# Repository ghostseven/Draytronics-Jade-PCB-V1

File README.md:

# Draytronics-Jade-PCB-V1

## Currently untested pre-production only.

An open source 65% mechanical keyboard, designed to be easily built with through hole components. More info / kits / PCB designs available at https://www.draytronics.co.uk/jade

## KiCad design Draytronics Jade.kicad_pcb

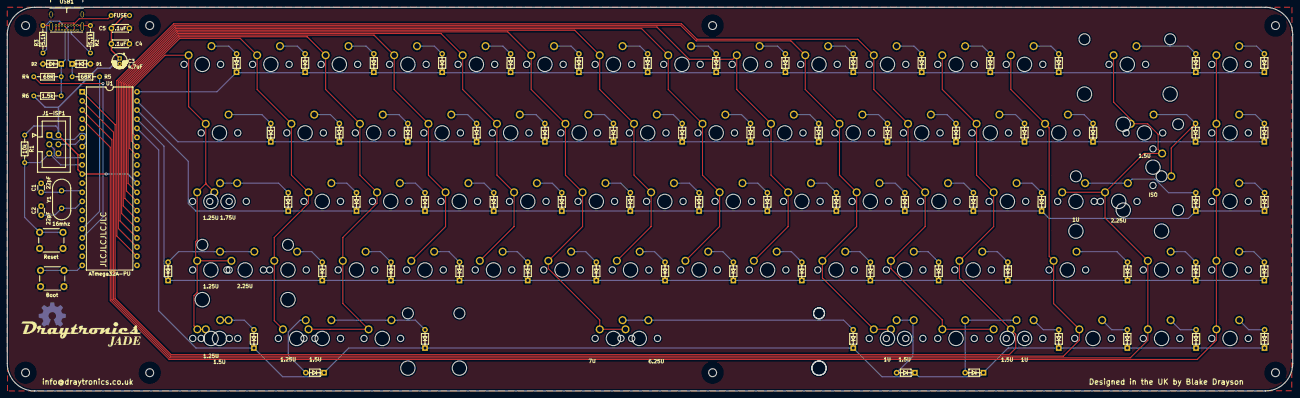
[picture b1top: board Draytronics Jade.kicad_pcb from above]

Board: 2 copper layers, 357.4 x 106.7 mm, 167 parts (0 on the bottom side), 105 nets.

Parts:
Boot1: Boot; SW_PUSH_6mm
C1, C2: 22pF; C_Disc_D3.0mm_W1.6mm_P2.50mm
C3: 4.7uF; CP_Radial_D4.0mm_P1.50mm
C4, C5: .1uF; C_Disc_D4.3mm_W1.9mm_P5.00mm
D1, D2: 3.6V; D_DO-35_SOD27_P5.08mm_Horizontal
D3, D4, D5, D6, D7, D8, D9, D10, D11, D12, D13, D14, D15, D16, D17, D18, D19, D20, D21, D22, D23, D24, D25, D26, D27, D28, D29, D30, D31, D32, D33, D34, D35, D36, D37, D38, D39, D40, D41, D42, D43, D44, D45, D46, D47, D48, D49, D50, D51, D52, D53, D54, D55, D56, D57, D58, D59, D60, D61, D62, D63, D64, D65, D66, D67, D68, D69, D70, D71: 1N4148; D_DO-35_SOD27_P5.08mm_Horizontal
F1: 500ma; polyfuse_5.1mm
J1-ISP1: AVR-ISP-6; IDC-Header_2x03_P2.54mm_Vertical
MX1, MX2, MX7, MX13: 1.25U; MXOnly-1.25U-NoLED
MX3, MX9, MX10, MX11, MX12, MX14, MX15, MX16, MX17, MX20, MX21, MX22, MX23, MX24, MX25, MX26, MX27, MX28, MX29, MX30, MX31, MX34, MX35, MX36, MX37, MX38, MX39, MX40, MX41, MX42, MX43, MX44, MX45, MX46, MX47, MX48, MX49, MX52, MX53, MX54, MX55, MX56, MX58, MX59, MX60, MX61, MX63, MX64, MX67, MX71, MX72, MX73, MX74, MX75, MX76, MX77: MX-NoLED; MXOnly-1U-NoLED
MX4: MX-NoLED; MXOnly-1.5U-NoLED
MX5: 1.75U; MXOnly-1.75U-NoLED
MX6, MX65: 2.25U; MXOnly-2.25U-NoLED
MX8, MX19, MX51, MX57, MX69: 1.5U; MXOnly-1.5U-NoLED
MX18: MX-NoLED; MXOnly-1.25U-NoLED
MX32: 6.25U; MXOnly-6.25U-NoLED
MX33: 7U; MXOnly-7U-NoLED
MX50, MX62, MX70: 1U; MXOnly-1U-NoLED
MX66: MX-NoLED; MXOnly-1.75U-NoLED
MX68: MX-NoLED; MXOnly-2U-NoLED
MX78: ISO; MXOnly-ISO-ROTATED-ReversedStabilizers-NoLED
R1: 10k; R_Axial_DIN0204_L3.6mm_D1.6mm_P7.62mm_Horizontal
R2, R3: 5.1k; R_Axial_DIN0204_L3.6mm_D1.6mm_P7.62mm_Horizontal
R4, R5: 68R; R_Axial_DIN0204_L3.6mm_D1.6mm_P7.62mm_Horizontal
R6: 1.5k; R_Axial_DIN0204_L3.6mm_D1.6mm_P7.62mm_Horizontal
Reset1: Reset; SW_PUSH_6mm
U1: ATmega32A-PU; DIP-40_W15.24mm
USB1: USB_C_Receptacle_USB2.0; USB_C_GCT_USB4085
Y1: Crystal; Crystal_HC49-U_Vertical

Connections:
+5V: C3.1, C4.1, C5.1, F1.1, J1-ISP1.2, R1.1, R6.1, U1.10, U1.30
D+: R5.1, U1.16
D-: R4.1, U1.17
GND: Boot1.1, C1.2, C2.2, C3.2, C4.2, C5.2, D1.2, D2.2, J1-ISP1.6, R2.1, R3.1, Reset1.1, U1.11, U1.31, USB1.A1, USB1.A12, USB1.B1, USB1.B12, USB1.S1
unnamed: C1.1, U1.12, Y1.2
unnamed: C2.1, U1.13, Y1.1
unnamed: D1.1, R5.2, USB1.A6, USB1.B6
unnamed: D2.1, R4.2, R6.2, USB1.A7, USB1.B7
unnamed: D3.2, MX3.2
unnamed: D4.2, MX4.2
unnamed: D5.2, MX1.2, MX5.2
unnamed: D6.2, MX2.2, MX6.2
unnamed: D7.2, MX7.2, MX8.2
unnamed: D8.2, MX9.2
unnamed: D9.2, MX10.2
unnamed: D10.2, MX11.2
unnamed: D11.2, MX12.2
unnamed: D12.2, MX13.2
unnamed: D13.2, MX14.2
unnamed: D14.2, MX15.2
unnamed: D15.2, MX16.2
unnamed: D16.2, MX17.2
unnamed: D17.2, MX18.2, MX19.2
unnamed: D18.2, MX20.2
unnamed: D19.2, MX21.2
unnamed: D20.2, MX22.2
unnamed: D21.2, MX23.2
unnamed: D22.2, MX24.2
unnamed: D23.2, MX25.2
unnamed: D24.2, MX26.2
unnamed: D25.2, MX27.2
unnamed: D26.2, MX28.2
unnamed: D27.2, MX29.2
unnamed: D28.2, MX30.2
unnamed: D29.2, MX31.2
unnamed: D30.2, MX32.2, MX33.2
unnamed: D31.2, MX34.2
unnamed: D32.2, MX35.2
unnamed: D33.2, MX36.2
unnamed: D34.2, MX37.2
unnamed: D35.2, MX38.2
unnamed: D36.2, MX39.2
unnamed: D37.2, MX40.2
unnamed: D38.2, MX41.2
unnamed: D39.2, MX42.2
unnamed: D40.2, MX43.2
unnamed: D41.2, MX44.2
unnamed: D42.2, MX45.2
unnamed: D43.2, MX46.2
unnamed: D44.2, MX47.2
unnamed: D45.2, MX48.2
unnamed: D46.2, MX49.2
unnamed: D47.2, MX50.2, MX51.2
unnamed: D48.2, MX52.2
unnamed: D49.2, MX53.2
unnamed: D50.2, MX54.2
unnamed: D51.2, MX55.2
unnamed: D52.2, MX56.2, MX57.2
unnamed: D53.2, MX58.2
unnamed: D54.2, MX59.2
unnamed: D55.2, MX60.2
unnamed: D56.2, MX61.2
unnamed: D57.2, MX62.2
unnamed: D58.2, MX63.2
unnamed: D59.2, MX64.2
unnamed: D60.2, MX66.2
unnamed: D61.2, MX67.2
unnamed: D62.2, MX68.2
unnamed: D63.2, MX69.2, MX78.2
unnamed: D64.2, MX65.2, MX70.2
unnamed: D65.2, MX71.2
unnamed: D66.2, MX72.2
unnamed: D67.2, MX73.2
unnamed: D68.2, MX74.2
unnamed: D69.2, MX75.2
unnamed: D70.2, MX76.2
unnamed: D71.2, MX77.2
unnamed: R2.2, USB1.A5
unnamed: R3.2, USB1.B5
VCC: F1.2, USB1.A4, USB1.A9, USB1.B4, USB1.B9
bload: Boot1.2, U1.20
col0: MX1.1, MX2.1, MX3.1, MX4.1, MX5.1, MX6.1, MX7.1, MX8.1, U1.35
col1: MX9.1, MX10.1, MX11.1, MX12.1, MX13.1, U1.34
col2: MX14.1, MX15.1, MX16.1, MX17.1, MX18.1, MX19.1, U1.33
col3: MX20.1, MX21.1, MX22.1, MX23.1, U1.29
col4: MX24.1, MX25.1, MX26.1, MX27.1, U1.28
col5: MX28.1, MX29.1, MX30.1, MX31.1, MX32.1, MX33.1, U1.27
col6: MX34.1, MX35.1, MX36.1, MX37.1, U1.26
col7: MX38.1, MX39.1, MX40.1, MX41.1, U1.25
col8: MX42.1, MX43.1, MX44.1, MX45.1, U1.24
col9: MX46.1, MX47.1, MX48.1, MX49.1, MX50.1, MX51.1, U1.23
col10: MX52.1, MX53.1, MX54.1, MX55.1, MX56.1, MX57.1, U1.22
col11: MX58.1, MX59.1, MX60.1, MX61.1, MX62.1, U1.1
col12: MX63.1, MX64.1, MX66.1, MX67.1, U1.2
col13: MX65.1, MX68.1, MX69.1, MX70.1, MX71.1, MX72.1, MX78.1, U1.3
col14: MX73.1, MX74.1, MX75.1, MX76.1, MX77.1, U1.4
miso: J1-ISP1.1, U1.7
mosi: J1-ISP1.4, U1.6
reset: J1-ISP1.5, R1.2, Reset1.2, U1.9
row0: D3.1, D8.1, D13.1, D18.1, D22.1, D26.1, D31.1, D35.1, D39.1, D43.1, D48.1, D53.1, D58.1, D62.1, D67.1, U1.40
row1: D4.1, D9.1, D14.1, D19.1, D23.1, D27.1, D32.1, D36.1, D40.1, D44.1, D49.1, D54.1, D59.1, D63.1, D68.1, U1.39
row2: D5.1, D10.1, D15.1, D20.1, D24.1, D28.1, D33.1, D37.1, D41.1, D45.1, D50.1, D55.1, D64.1, D69.1, U1.38
row3: D6.1, D11.1, D16.1, D21.1, D25.1, D29.1, D34.1, D38.1, D42.1, D46.1, D51.1, D56.1, D60.1, D65.1, D70.1, U1.37
row4: D7.1, D12.1, D17.1, D30.1, D47.1, D52.1, D57.1, D61.1, D66.1, D71.1, U1.36
sck: J1-ISP1.3, U1.8

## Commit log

2020-12-29 Readme Update
2020-12-29 Readme update.
2020-12-30 Added PCB renders
2021-02-03 Added middle standoff for stability
